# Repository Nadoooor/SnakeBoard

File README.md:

# SnakeBoard
It is a custom keycool84 size keyboard with dual oled screens and a rotary encoder.<br>
I made this project to improve my cad skills and pcb designing skills. Also, i need a good keyboard to write my homework with.<br>
The Onshape Doc: [DOC](https://cad.onshape.com/documents/902611e8b9feae564de8d9eb/w/ee044899b2f02c71afc87682/e/73f01ff6e236a97137583ab3?renderMode=0&uiState=688221b8a27d1511c8890300)<br>

## Photos:
### Schematic:

### PCB:

### 3D PCB:

### Final Case:

## BOM for SnakeBoard:
| Part name                                               | link                                                                                                                                                                                                                                                                                                                                                                                                                                                                                                                                                                                     | price  |
|---------------------------------------------------------|------------------------------------------------------------------------------------------------------------------------------------------------------------------------------------------------------------------------------------------------------------------------------------------------------------------------------------------------------------------------------------------------------------------------------------------------------------------------------------------------------------------------------------------------------------------------------------------|--------|
| Key Switches x4 packs                                            | [Link](https://www.amazon.eg/-/en/gp/product/B09QGQVQYD/ref=ox_sc_act_title_2?smid=A1ZVRGNO5AYLOV&psc=1)                                                                                                                                                                                                          | $43.83 |
| keycaps                                                 | [Link](https://www.amazon.eg/-/en/Redragon-A101-Double-Shot-mechanical-keyboard/dp/B019OAQ6VI/ref=sr_1_3?crid=1EDSB6B359962&dib=eyJ2IjoiMSJ9.wD7VG1MxwQYx9D6YZqPVxtJ1dFIRSeLMF1gmMGVc2lEYu6347Eqi5hz-yUdAzJEr2D08Qv5ngxRmC2Et3NeRO3K2PAWTfF5ZD7dNvIEBvW3J1swA5LjqBNs8g4VxE9ZDNfC-B1ejkWkmNnq1BzCwhzCFhgQ6T9OL5aTMCvT84dIu3x3KgPLGUDi6wlub9ozFmAsrms-6uFClVkwS0dtkmJ68mgQ7EsXc4K9x9jGzLsAx8HFuH43_fH5Em_Ksyy7WvJcEOgssqWDP3yWDiAt0Dzbg7hDAQYc_JxO5Egab-UY.QSRC6Wm2rXR7-xzCP1SevjA28SaDu6sTpjRap5sIYkk&dib_tag=se&keywords=keycaps&qid=1753464766&sprefix=keycaps%2Caps%2C178&sr=8-3&th=1) | $7.72  |
| Zener Diode BZX79-C5V1 (6.2 Volt)                       | [Link](https://mostelectronic.com/shop/components/diodes/zener-diode-bzx79-c5v1-6-2-volt/)                                                                                                                                                                                                                                                                                                                                                                                                                                                                                               | $0.92  |
| Solder Wire Singapore 25g (0.6mm -70/30) Singapore      | [Link](https://mostelectronic.com/shop/tools/soldering-desoldering/solder-wire-singapore-25g-0-6mm-70-30-singapore/)                                                                                                                                                                                                                                                                                                                                                                                                                                                                     | $1.53  |
| OLED LCD LED Display Module White (128X64) 0.96 inch)   | [Link](https://mostelectronic.com/shop/displays-lcd-7-seg-led/lcd-modules-displays-lcd-7-seg-led/0-96%e2%80%b3-oled-4pin-lcd-led-display-module-i2c-iic-communicate-white-128x64/)                                                                                                                                                                                                                                                                                                                                                                                                       | $6.25  |
| Rotary encoder                            | [Link](https://mostelectronic.com/shop/sensors/ec11-rotary-encoder-with-push-button-switch-5pin-15mm/)                                                                                                                                                                                                                                                                                                                                                                                                                                                                | $0.5  |
| Raspberry pi pico                                       | [Link](https://mostelectronic.com/shop/arduino-development-boards/raspberry-pi/raspberry-pi-pico/)                                                                                                                                                                                                                                                                                                                                                                                                                                                                                       | $10    |
| Shift register                           |[Link](https://www.ram-e-shop.com/shop/74hc165-ic-74165-8-bit-parallel-in-serial-out-shift-register-6231)                                                                                                                                                                                                                                                                                                                                                                                                                                                                              | $0.31  |
| Total JLCPCb with shipping|  | $30 |
| shipping for most electronics                           |                                                                                                                                                                                                                                                                                                                                                                                                                                                                                                                                                                                          | $3.06  |
| shipping for amazon eg                                  |                                                                                                                                                                                                                                                                                                                                                                                                                                                                                                                                                                                          | $2     |
| 3D Printed case                                         |                                                                                                                                                                                                                                                                                                                                                                                                                                                                                                                                                                                          | $36.10 |
| Total                                                   |                                                                                                                                                                                                                                                        | $141.59|

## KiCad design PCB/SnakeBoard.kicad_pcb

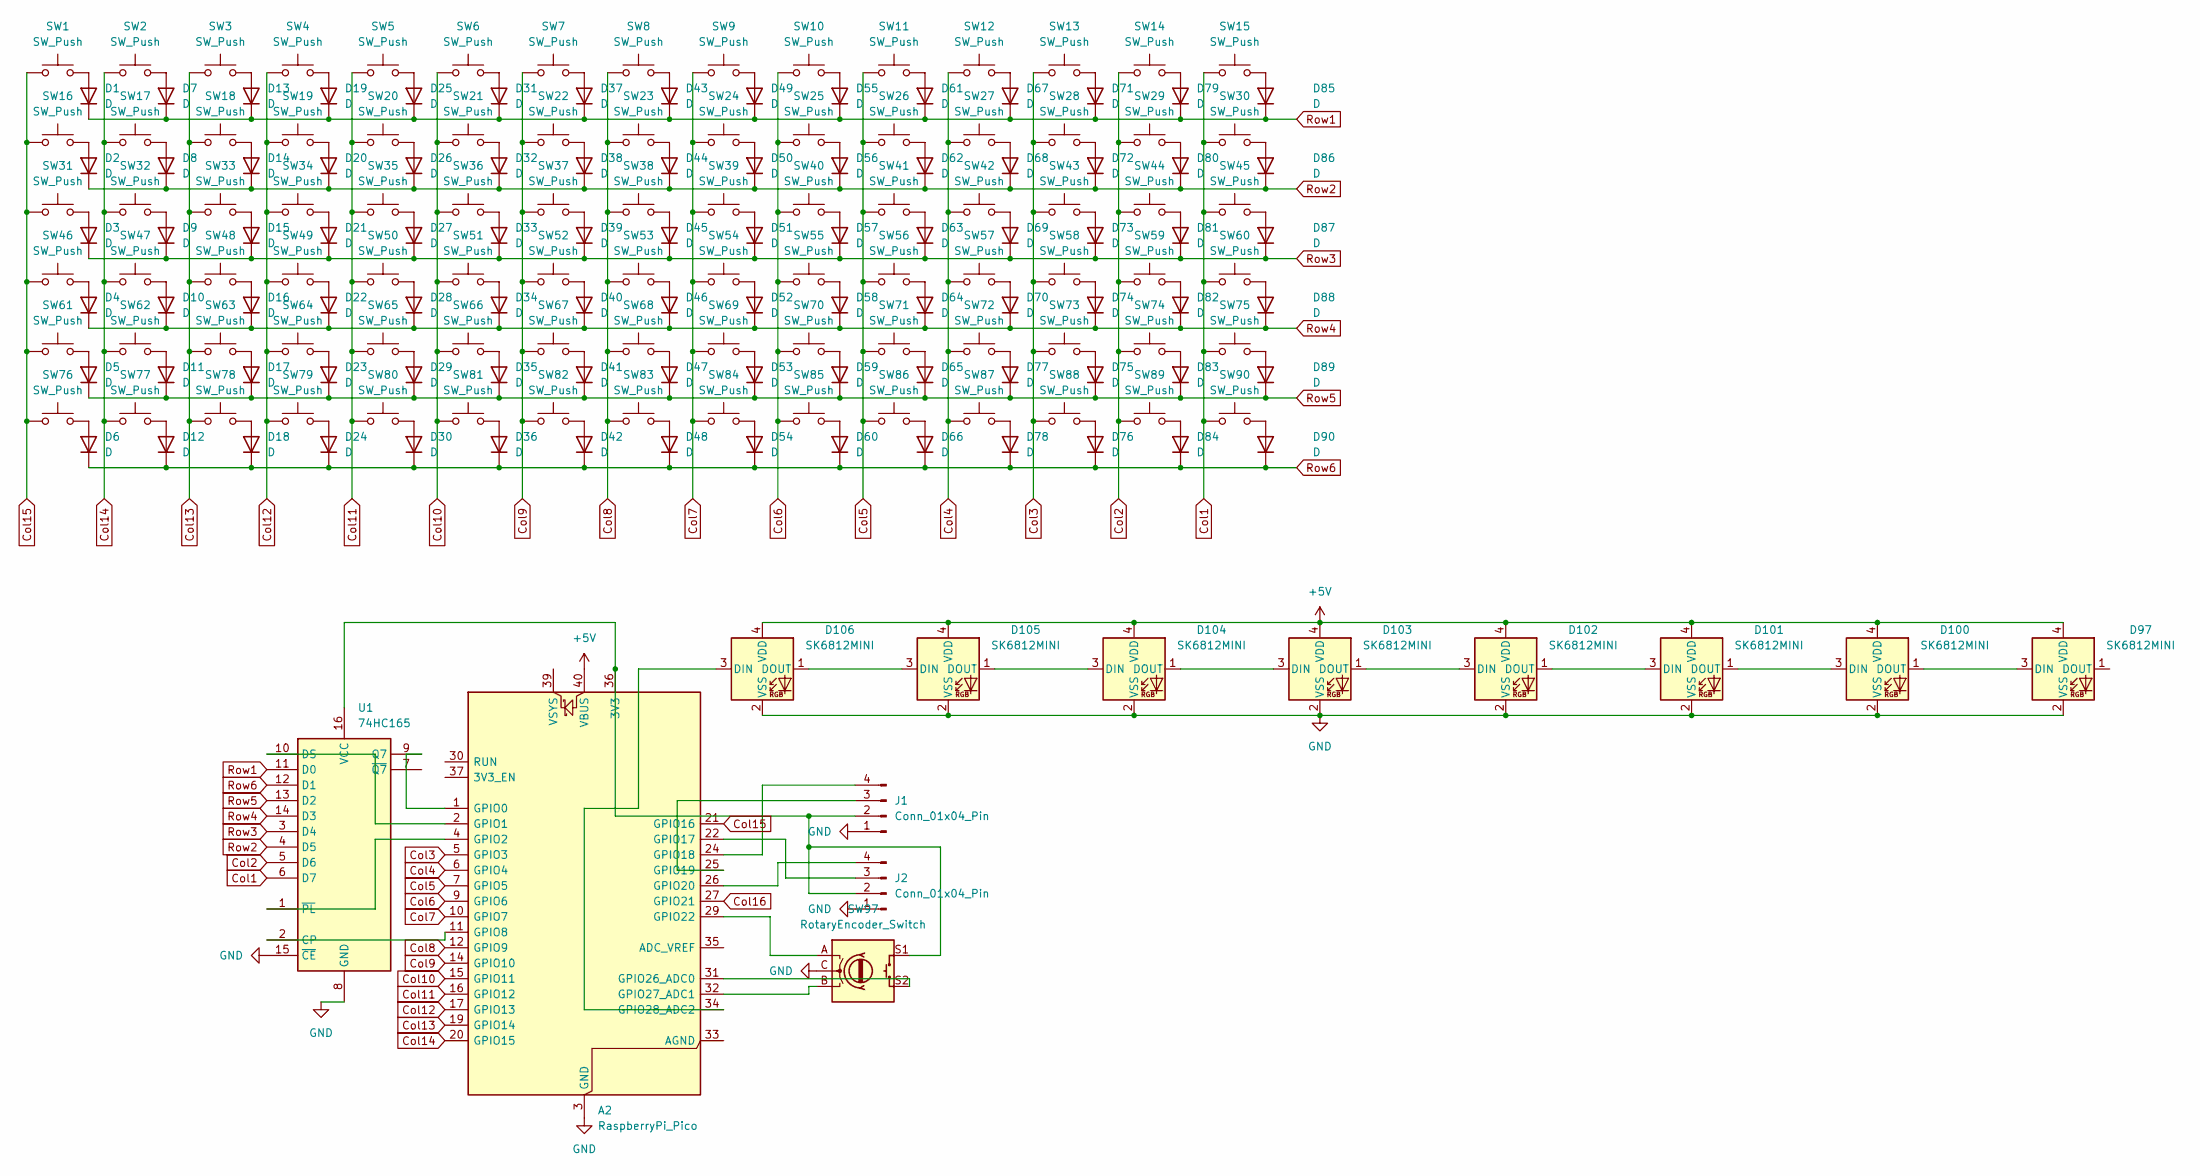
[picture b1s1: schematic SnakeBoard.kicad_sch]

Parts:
A2: RaspberryPi_Pico; RaspberryPi_Pico_Common_Unspecified
D1, D2, D3, D4, D5, D6, D7, D8, D9, D10, D11, D12, D13, D14, D15, D16, D17, D18, D19, D20, D21, D22, D23, D24, D25, D26, D27, D28, D29, D30, D31, D32, D33, D34, D35, D36, D37, D38, D39, D40, D41, D42, D43, D44, D45, D46, D47, D48, D49, D50, D51, D52, D53, D54, D55, D56, D57, D58, D59, D60, D61, D62, D63, D64, D65, D66, D67, D68, D69, D70, D71, D72, D73, D74, D75, D76, D77, D78, D79, D80, D81, D82, D83, D84, D85, D86, D87, D88, D89, D90: D; D_DO-35_SOD27_P7.62mm_Horizontal
D97, D100, D101, D102, D103, D104, D105, D106: SK6812MINI; LED_SK6812MINI_PLCC4_3.5x3.5mm_P1.75mm
J1, J2: Conn_01x04_Pin; SSD1306_0.96_Oled
SW1, SW2, SW3, SW4, SW5, SW6, SW7, SW8, SW9, SW10, SW11, SW12, SW13, SW14, SW15, SW16, SW17, SW18, SW19, SW20, SW21, SW22, SW23, SW24, SW25, SW26, SW27, SW28, SW29, SW30, SW31, SW32, SW33, SW34, SW35, SW36, SW37, SW38, SW39, SW40, SW41, SW42, SW43, SW44, SW45, SW46, SW47, SW48, SW49, SW50, SW51, SW52, SW53, SW54, SW55, SW56, SW57, SW58, SW59, SW60, SW61, SW62, SW63, SW64, SW65, SW66, SW67, SW68, SW69, SW70, SW71, SW72, SW73, SW74, SW75, SW76, SW77, SW78, SW79, SW80, SW81, SW82, SW83, SW84, SW85, SW86, SW87, SW88, SW89, SW90: SW_Push; SW_Cherry_MX_1.00u_PCB
SW97: RotaryEncoder_Switch; RotaryEncoder_Alps_EC12E-Switch_Vertical_H20mm
U1: 74HC165; DIP-16_W7.62mm

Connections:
+5V: A2.40 (VBUS), D97.4 (VDD), D100.4 (VDD), D101.4 (VDD), D102.4 (VDD), D103.4 (VDD), D104.4 (VDD), D105.4 (VDD), D106.4 (VDD)
Col1: SW15.1, SW30.1, SW45.1, SW60.1, SW75.1, SW90.1, U1.6 (D7)
Col2: SW14.1, SW29.1, SW44.1, SW59.1, SW74.1, SW89.1, U1.5 (D6)
Col3: A2.5 (GPIO3), SW13.1, SW28.1, SW43.1, SW58.1, SW73.1, SW88.1
Col4: A2.6 (GPIO4), SW12.1, SW27.1, SW42.1, SW57.1, SW72.1, SW87.1
Col5: A2.7 (GPIO5), SW11.1, SW26.1, SW41.1, SW56.1, SW71.1, SW86.1
Col6: A2.9 (GPIO6), SW10.1, SW25.1, SW40.1, SW55.1, SW70.1, SW85.1
Col7: A2.10 (GPIO7), SW9.1, SW24.1, SW39.1, SW54.1, SW69.1, SW84.1
Col8: A2.12 (GPIO9), SW8.1, SW23.1, SW38.1, SW53.1, SW68.1, SW83.1
Col9: A2.14 (GPIO10), SW7.1, SW22.1, SW37.1, SW52.1, SW67.1, SW82.1
Col10: A2.15 (GPIO11), SW6.1, SW21.1, SW36.1, SW51.1, SW66.1, SW81.1
Col11: A2.16 (GPIO12), SW5.1, SW20.1, SW35.1, SW50.1, SW65.1, SW80.1
Col12: A2.17 (GPIO13), SW4.1, SW19.1, SW34.1, SW49.1, SW64.1, SW79.1
Col13: A2.19 (GPIO14), SW3.1, SW18.1, SW33.1, SW48.1, SW63.1, SW78.1
Col14: A2.20 (GPIO15), SW2.1, SW17.1, SW32.1, SW47.1, SW62.1, SW77.1
Col15: A2.21 (GPIO16), SW1.1, SW16.1, SW31.1, SW46.1, SW61.1, SW76.1
Col16: A2.27 (GPIO21)
GND: A2.3 (GND), A2.8 (GND), A2.13 (GND), A2.18 (GND), A2.23 (GND), A2.28 (GND), A2.38 (GND), D97.2 (VSS), D100.2 (VSS), D101.2 (VSS), D102.2 (VSS), D103.2 (VSS), D104.2 (VSS), D105.2 (VSS), D106.2 (VSS), J1.1, J2.1, SW97.C, U1.8 (GND), U1.15 (~CE)
unnamed: A2.36 (3V3), J1.2, J2.2, SW97.S1, U1.16 (VCC)
unnamed: A2.1 (GPIO0), U1.9 (Q7)
unnamed: A2.2 (GPIO1), U1.10 (DS)
unnamed: A2.4 (GPIO2), U1.1 (~PL)
unnamed: A2.11 (GPIO8), U1.2 (CP)
unnamed: A2.22 (GPIO17), J2.3
unnamed: A2.24 (GPIO18), J1.4
unnamed: A2.25 (GPIO19), J1.3
unnamed: A2.26 (GPIO20), J2.4
unnamed: A2.29 (GPIO22), SW97.A
unnamed: A2.31 (GPIO26_ADC0), SW97.S2
unnamed: A2.32 (GPIO27_ADC1), SW97.B
unnamed: A2.34 (GPIO28_ADC2), D106.3 (DIN)
unnamed: D1.2 (A), SW1.2
unnamed: D2.2 (A), SW16.2
unnamed: D3.2 (A), SW31.2
unnamed: D4.2 (A), SW46.2
unnamed: D5.2 (A), SW61.2
unnamed: D6.2 (A), SW76.2
unnamed: D7.2 (A), SW2.2
unnamed: D8.2 (A), SW17.2
unnamed: D9.2 (A), SW32.2
unnamed: D10.2 (A), SW47.2
unnamed: D11.2 (A), SW62.2
unnamed: D12.2 (A), SW77.2
unnamed: D13.2 (A), SW3.2
unnamed: D14.2 (A), SW18.2
unnamed: D15.2 (A), SW33.2
unnamed: D16.2 (A), SW48.2
unnamed: D17.2 (A), SW63.2
unnamed: D18.2 (A), SW78.2
unnamed: D19.2 (A), SW4.2
unnamed: D20.2 (A), SW19.2
unnamed: D21.2 (A), SW34.2
unnamed: D22.2 (A), SW49.2
unnamed: D23.2 (A), SW64.2
unnamed: D24.2 (A), SW79.2
unnamed: D25.2 (A), SW5.2
unnamed: D26.2 (A), SW20.2
unnamed: D27.2 (A), SW35.2
unnamed: D28.2 (A), SW50.2
unnamed: D29.2 (A), SW65.2
unnamed: D30.2 (A), SW80.2
unnamed: D31.2 (A), SW6.2
unnamed: D32.2 (A), SW21.2
unnamed: D33.2 (A), SW36.2
unnamed: D34.2 (A), SW51.2
unnamed: D35.2 (A), SW66.2
unnamed: D36.2 (A), SW81.2
unnamed: D37.2 (A), SW7.2
unnamed: D38.2 (A), SW22.2
unnamed: D39.2 (A), SW37.2
unnamed: D40.2 (A), SW52.2
unnamed: D41.2 (A), SW67.2
unnamed: D42.2 (A), SW82.2
unnamed: D43.2 (A), SW8.2
unnamed: D44.2 (A), SW23.2
unnamed: D45.2 (A), SW38.2
unnamed: D46.2 (A), SW53.2
unnamed: D47.2 (A), SW68.2
unnamed: D48.2 (A), SW83.2
unnamed: D49.2 (A), SW9.2
unnamed: D50.2 (A), SW24.2
unnamed: D51.2 (A), SW39.2
unnamed: D52.2 (A), SW54.2
unnamed: D53.2 (A), SW69.2
unnamed: D54.2 (A), SW84.2
unnamed: D55.2 (A), SW10.2
unnamed: D56.2 (A), SW25.2
unnamed: D57.2 (A), SW40.2
unnamed: D58.2 (A), SW55.2
unnamed: D59.2 (A), SW70.2
unnamed: D60.2 (A), SW85.2
unnamed: D61.2 (A), SW11.2
unnamed: D62.2 (A), SW26.2
unnamed: D63.2 (A), SW41.2
unnamed: D64.2 (A), SW56.2
unnamed: D65.2 (A), SW71.2
unnamed: D66.2 (A), SW86.2
unnamed: D67.2 (A), SW12.2
unnamed: D68.2 (A), SW27.2
unnamed: D69.2 (A), SW42.2
unnamed: D70.2 (A), SW57.2
unnamed: D71.2 (A), SW13.2
unnamed: D72.2 (A), SW28.2
unnamed: D73.2 (A), SW43.2
unnamed: D74.2 (A), SW58.2
unnamed: D75.2 (A), SW73.2
unnamed: D76.2 (A), SW88.2
unnamed: D77.2 (A), SW72.2
unnamed: D78.2 (A), SW87.2
unnamed: D79.2 (A), SW14.2
unnamed: D80.2 (A), SW29.2
unnamed: D81.2 (A), SW44.2
unnamed: D82.2 (A), SW59.2
unnamed: D83.2 (A), SW74.2
unnamed: D84.2 (A), SW89.2
unnamed: D85.2 (A), SW15.2
unnamed: D86.2 (A), SW30.2
unnamed: D87.2 (A), SW45.2
unnamed: D88.2 (A), SW60.2
unnamed: D89.2 (A), SW75.2
unnamed: D90.2 (A), SW90.2
unnamed: D100.3 (DIN), D101.1 (DOUT)
unnamed: D97.3 (DIN), D100.1 (DOUT)
unnamed: D101.3 (DIN), D102.1 (DOUT)
unnamed: D102.3 (DIN), D103.1 (DOUT)
unnamed: D103.3 (DIN), D104.1 (DOUT)
unnamed: D104.3 (DIN), D105.1 (DOUT)
unnamed: D105.3 (DIN), D106.1 (DOUT)
Row1: D1.1 (K), D7.1 (K), D13.1 (K), D19.1 (K), D25.1 (K), D31.1 (K), D37.1 (K), D43.1 (K), D49.1 (K), D55.1 (K), D61.1 (K), D67.1 (K), D71.1 (K), D79.1 (K), D85.1 (K), U1.11 (D0)
Row2: D2.1 (K), D8.1 (K), D14.1 (K), D20.1 (K), D26.1 (K), D32.1 (K), D38.1 (K), D44.1 (K), D50.1 (K), D56.1 (K), D62.1 (K), D68.1 (K), D72.1 (K), D80.1 (K), D86.1 (K), U1.4 (D5)
Row3: D3.1 (K), D9.1 (K), D15.1 (K), D21.1 (K), D27.1 (K), D33.1 (K), D39.1 (K), D45.1 (K), D51.1 (K), D57.1 (K), D63.1 (K), D69.1 (K), D73.1 (K), D81.1 (K), D87.1 (K), U1.3 (D4)
Row4: D4.1 (K), D10.1 (K), D16.1 (K), D22.1 (K), D28.1 (K), D34.1 (K), D40.1 (K), D46.1 (K), D52.1 (K), D58.1 (K), D64.1 (K), D70.1 (K), D74.1 (K), D82.1 (K), D88.1 (K), U1.14 (D3)
Row5: D5.1 (K), D11.1 (K), D17.1 (K), D23.1 (K), D29.1 (K), D35.1 (K), D41.1 (K), D47.1 (K), D53.1 (K), D59.1 (K), D65.1 (K), D75.1 (K), D77.1 (K), D83.1 (K), D89.1 (K), U1.13 (D2)
Row6: D6.1 (K), D12.1 (K), D18.1 (K), D24.1 (K), D30.1 (K), D36.1 (K), D42.1 (K), D48.1 (K), D54.1 (K), D60.1 (K), D66.1 (K), D76.1 (K), D78.1 (K), D84.1 (K), D90.1 (K), U1.12 (D1)

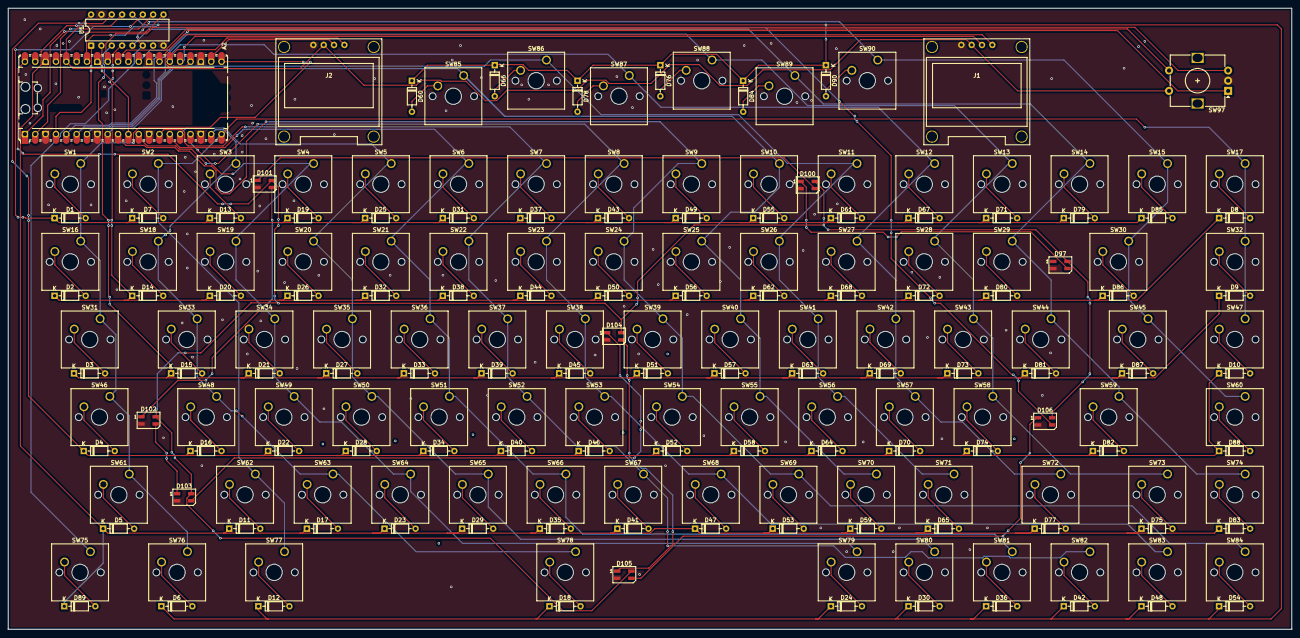
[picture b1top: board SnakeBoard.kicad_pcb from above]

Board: 2 copper layers, 315.0 x 152.4 mm, 193 parts (0 on the bottom side), 133 nets.

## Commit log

2025-06-26 Test Commit
2025-06-27 add the switches
2025-06-29 add teh schematic changes
2025-06-30 Add the schematic
2025-06-30 Added the PCB remains the routing
2025-06-30 Add to the JOURNAL
2025-06-30 Finished the PCB and it is all done.
2025-07-16 ADdd
2025-07-28 Rename plate.step to Production/Case/plate.step
2025-07-28 Rename bottom(1).step to Production/Case/bottom.step
2025-07-28 Rename Production/SnakeBoard.zip to Production/PCB/SnakeBoard.zip
2025-08-02 Rename tableConvert.com_jnz7wg.csv to BOM.csv
